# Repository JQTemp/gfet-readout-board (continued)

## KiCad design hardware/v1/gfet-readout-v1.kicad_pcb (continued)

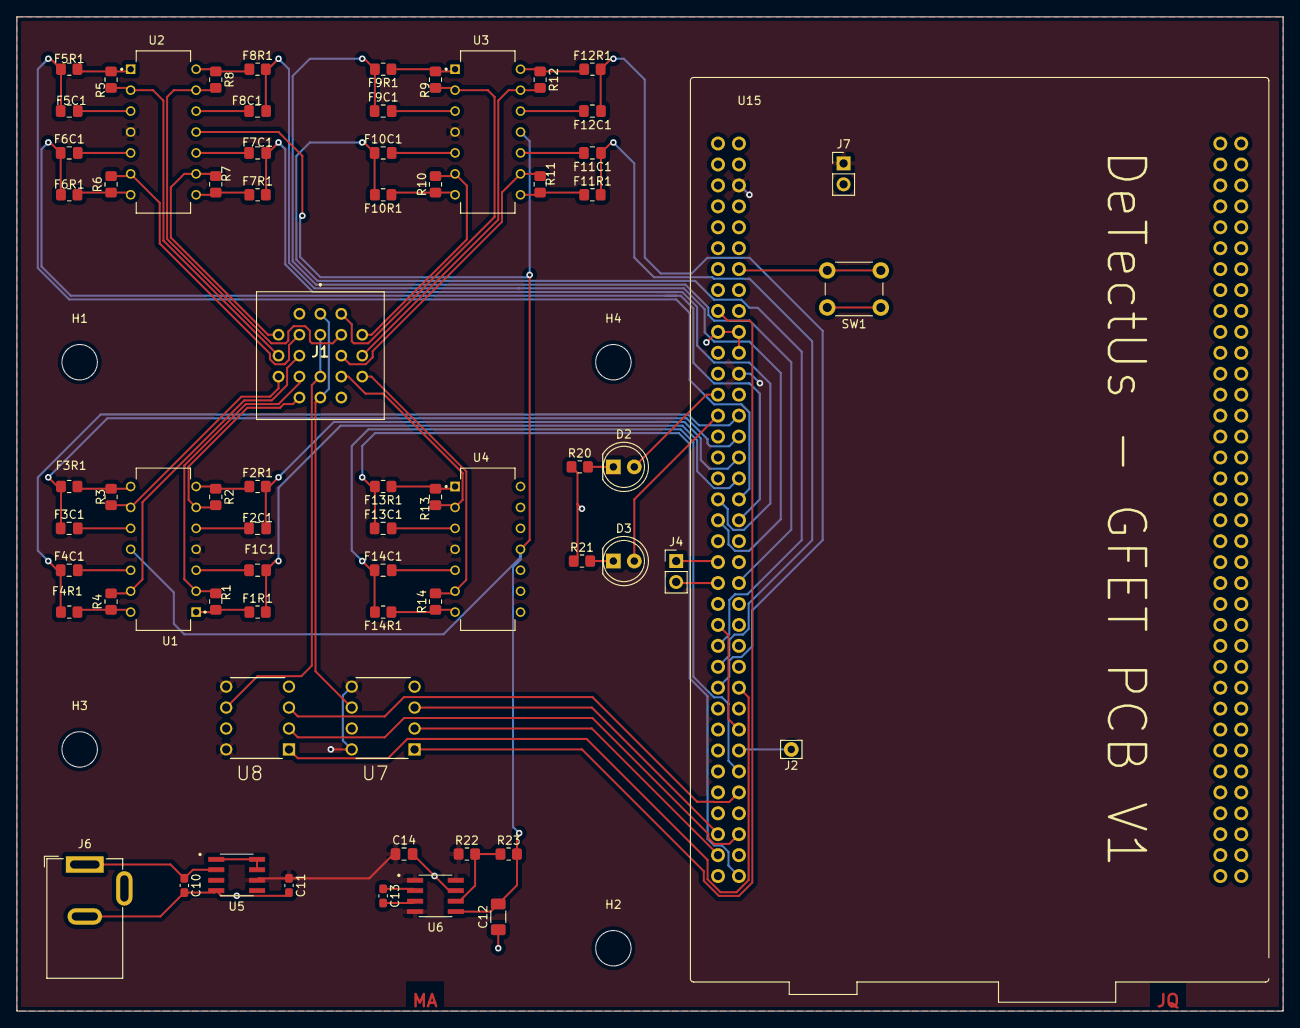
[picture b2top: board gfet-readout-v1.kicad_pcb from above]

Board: 2 copper layers, 153.7 x 120.7 mm, 72 parts (0 on the bottom side), 66 nets.
